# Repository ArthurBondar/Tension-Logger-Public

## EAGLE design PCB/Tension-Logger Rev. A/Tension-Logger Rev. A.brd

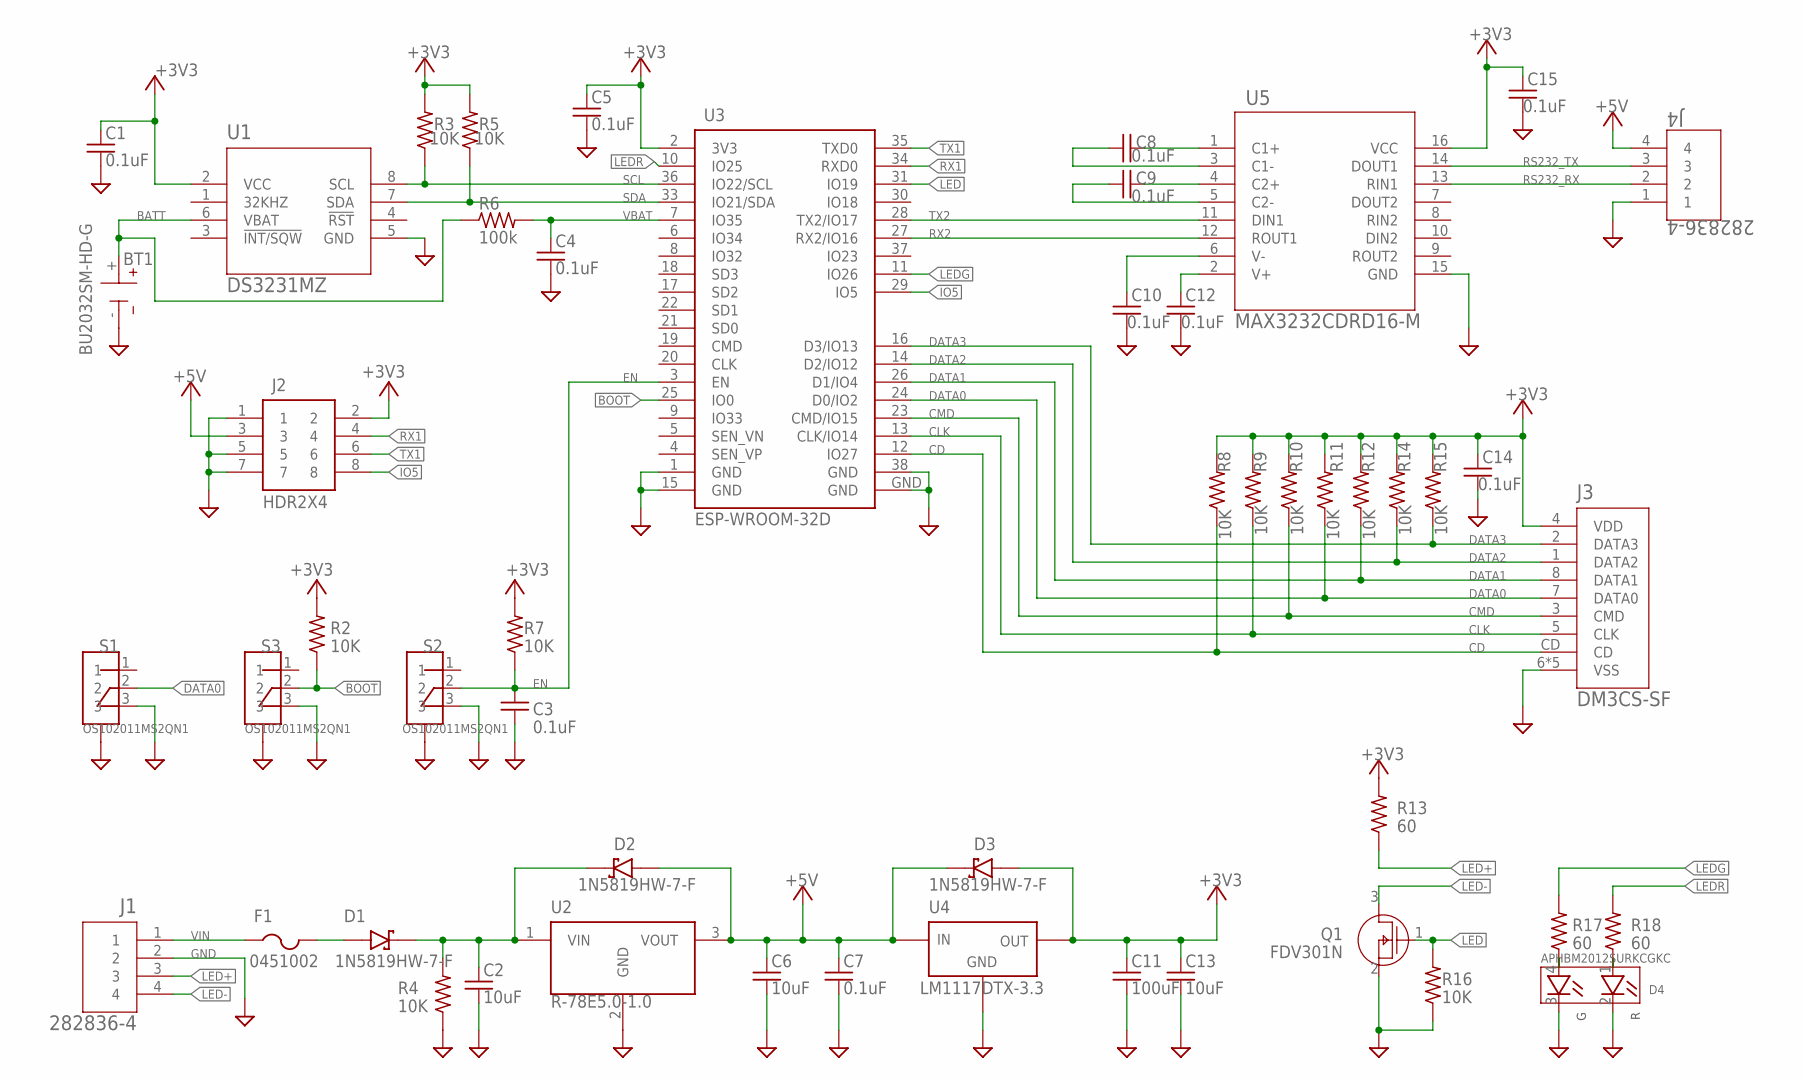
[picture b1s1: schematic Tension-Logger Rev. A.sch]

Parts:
BT1: BU2032SM-HD-G; BAT_BU2032SM-HD-G
C1, C3, C4, C5, C7, C8, C9, C10, C12, C14, C15: 0.1uF; 0805
C2, C6: 10uF; 0805
C11: 100uF; 1210
C13: 10uF; 1210
D1, D2, D3: 1N5819HW-7-F; SOD3715X145N
D4: APHBM2012SURKCGKC; LED_APHBM2012SURKCGKC
F1: 0451002; FUSC6131X270
J1, J4: 282836-4; 282836-4_TYC
J2: HDR2X4
J3: DM3CS-SF; CONN_3CS-SF
Q1: FDV301N; SOT23-3_ONS
R2, R3, R4, R5, R7, R8, R9, R10, R11, R12, R14, R15, R16: 10K; R0805
R6: 100k; R0805
R13, R17, R18: 60; R0805
S1, S2, S3: OS102011MS2QN1; SW_OS102011MS2QN1
U1: DS3231MZ; 21-0041B_8_MXM-M
U2: R-78E5.0-1.0; CONV_R-78E5.0-1.0
U3: ESP-WROOM-32D; ESP-WROOM-32
U4: LM1117DTX-3.3; TO252
U5: MAX3232CDRD16-M; D16-M

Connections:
+3V3: C1.B (2), C5.B (2), C11.A (1), C13.A (1), C14.A (1), C15.B (2), D3.A, J2.2, J3.4 (VDD), R2.2, R3.2, R5.2, R7.2, R8.2, R9.2, R10.2, R11.2, R12.2, R13.2, R14.2, R15.2, U1.2 (VCC), U3.2 (3V3), U4.TAB (OUT), U5.16 (VCC)
+5V: C6.A (1), C7.A (1), D2.A, D3.C (K), J2.3, J4.4, U2.3 (VOUT), U4.2 (IN)
BATT: BT1.+, R6.1, U1.6 (VBAT)
BOOT: R2.1, S3.2, U3.25 (IO0)
CD: J3.CD, R8.1, U3.12 (IO27)
CLK: J3.5 (CLK), R9.1, U3.13 (CLK/IO14)
CMD: J3.3 (CMD), R10.1, U3.23 (CMD/IO15)
DATA0: J3.7 (DATA0), R11.1, S1.2, U3.24 (D0/IO2)
DATA1: J3.8 (DATA1), R12.1, U3.26 (D1/IO4)
DATA2: J3.1 (DATA2), R14.1, U3.14 (D2/IO12)
DATA3: J3.2 (DATA3), R15.1, U3.16 (D3/IO13)
EN: C3.B (2), R7.1, S2.2, U3.3 (EN)
GND: BT1.-, C1.A (1), C2.B (2), C3.A (1), C4.A (1), C5.A (1), C6.B (2), C7.B (2), C10.B (2), C11.B (2), C12.B (2), C13.B (2), C14.B (2), C15.A (1), D4.2 (C_R), D4.3 (C_G), J1.2, J2.1, J2.5, J2.7, J3.6 (VSS), J3.GND-1 (VSS), J3.GND-2 (VSS), J3.GND-3 (VSS), J3.GND-4 (VSS), J4.1, Q1.2 (S), R4.1, R16.1, S1.3, S1.M1 (CASE), S1.M2 (CASE), S2.3, S2.M1 (CASE), S2.M2 (CASE), S3.3, S3.M1 (CASE), S3.M2 (CASE), U1.5 (GND), U2.2 (GND), U3.1 (GND), U3.15 (GND), U3.38 (GND), U3.GND, U4.1 (GND), U5.15 (GND)
IO5: J2.8, U3.29 (IO5)
LED: Q1.1 (G), R16.2, U3.31 (IO19)
LED+: J1.3, R13.1
LED-: J1.4, Q1.3 (D)
LEDG: R17.2, U3.11 (IO26)
LEDR: R18.2, U3.10 (IO25)
unnamed: D1.A, F1.2
unnamed: D4.1 (A_R), R18.1
unnamed: C2.A (1), D1.C (K), D2.C (K), R4.2, U2.1 (VIN)
unnamed: D4.4 (A_G), R17.1
unnamed: C8.B (2), U5.1 (C1+)
unnamed: C8.A (1), U5.3 (C1-)
unnamed: C9.B (2), U5.4 (C2+)
unnamed: C9.A (1), U5.5 (C2-)
unnamed: C12.A (1), U5.2 (V+)
unnamed: C10.A (1), U5.6 (V-)
RS232_RX: J4.2, U5.13 (RIN1)
RS232_TX: J4.3, U5.14 (DOUT1)
RX1: J2.4, U3.34 (RXD0)
RX2: U3.27 (RX2/IO16), U5.12 (ROUT1)
SCL: R3.1, U1.8 (SCL), U3.36 (IO22/SCL)
SDA: R5.1, U1.7 (SDA), U3.33 (IO21/SDA)
TX1: J2.6, U3.35 (TXD0)
TX2: U3.28 (TX2/IO17), U5.11 (DIN1)
VBAT: C4.B (2), R6.2, U3.7 (IO35)
VIN: F1.1, J1.1

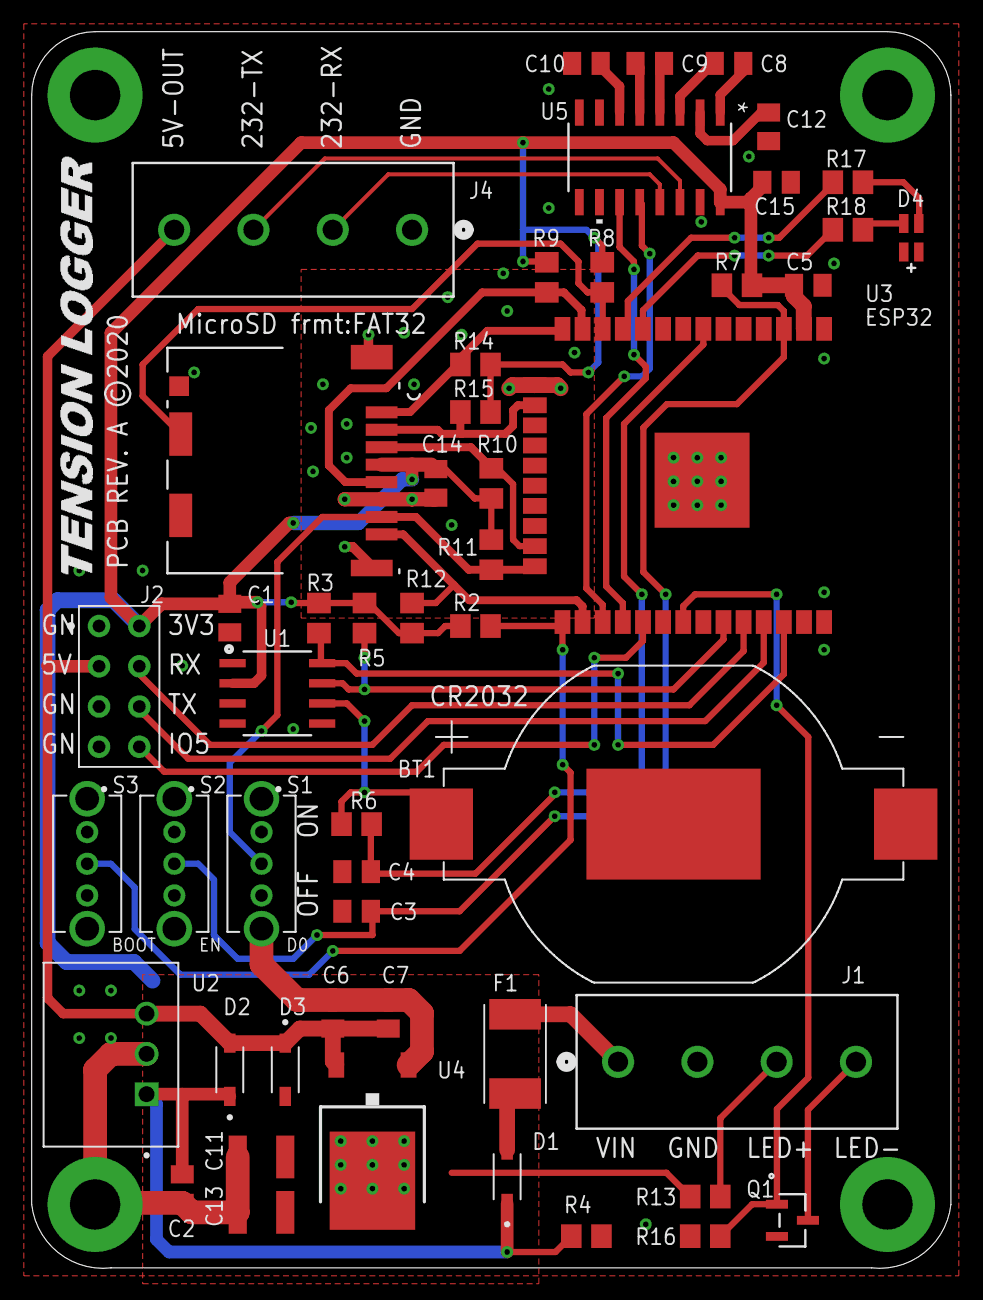
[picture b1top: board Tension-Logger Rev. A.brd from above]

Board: 2 copper layers, 58.0 x 78.0 mm, 51 parts (0 on the bottom side), 39 nets.

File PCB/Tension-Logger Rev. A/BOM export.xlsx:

Qty | Value | Device | Package | Parts
11 | 0.1uF | C0805 | 0805 | C1, C3, C4, C5, C7, C8, C9, C10, C12, C14, C15
1 | 0451002 | 0451002_MRL6.1_2.69_2.69MM | FUSC6131X270 | F1
1 | 100k | R-US_R0805 | R0805 | R6
1 | 100uF | C1210 | 1210 | C11
13 | 10K | R-US_R0805 | R0805 | R2, R3, R4, R5, R7, R8, R9, R10, R11, R12, R14, R15, R16
2 | 10uF | C0805 | 0805 | C2, C6
1 | 10uF | C1210 | 1210 | C13
3 | 1N5819HW-7-F | 1N5819HW-7-F | SOD3715X145N | D1, D2, D3
2 | 282836-4 | 282836-4 | 282836-4_TYC | J1, J4
3 | 60 | R-US_R0805 | R0805 | R13, R17, R18
1 | APHBM2012SURKCGKC | APHBM2012SURKCGKC | LED_APHBM2012SURKCGKC | D4
1 | BU2032SM-HD-G | BU2032SM-HD-G | BAT_BU2032SM-HD-G | BT1
1 | DM3CS-SF | DM3CS-SF | CONN_3CS-SF | J3
1 | DS3231MZ | DS3231MZ+21-0041B_8_MXM-M | 21-0041B_8_MXM-M | U1
1 | ESP-WROOM-32D | ESP-WROOM-32 | ESP-WROOM-32 | U3
1 | FDV301N | FDV301N | SOT23-3_ONS | Q1
1 | HDR2X4 | HDR2X4 | HDR2X4 | J2
1 | LM1117DTX-3.3 | LM1117DTX-3.3 | TO252 | U4
1 | MAX3232CDRD16-M | MAX3232CDRD16-M | D16-M | U5
3 | OS102011MS2QN1 | OS102011MS2QN1 | SW_OS102011MS2QN1 | S1, S2, S3
1 | R-78E5.0-1.0 | R-78E5.0-1.0 | CONV_R-78E5.0-1.0 | U2

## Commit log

2024-05-27 Making the project public, original files from March, 2021

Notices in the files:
PCB/Tension-Logger Rev. A/Tension-Logger Rev. A.brd:
PCB REV. A ©2020
parts and their libraries:
COPYRIGHT: Copyright (C) 2018 Accelerated Designs. All rights reserved
